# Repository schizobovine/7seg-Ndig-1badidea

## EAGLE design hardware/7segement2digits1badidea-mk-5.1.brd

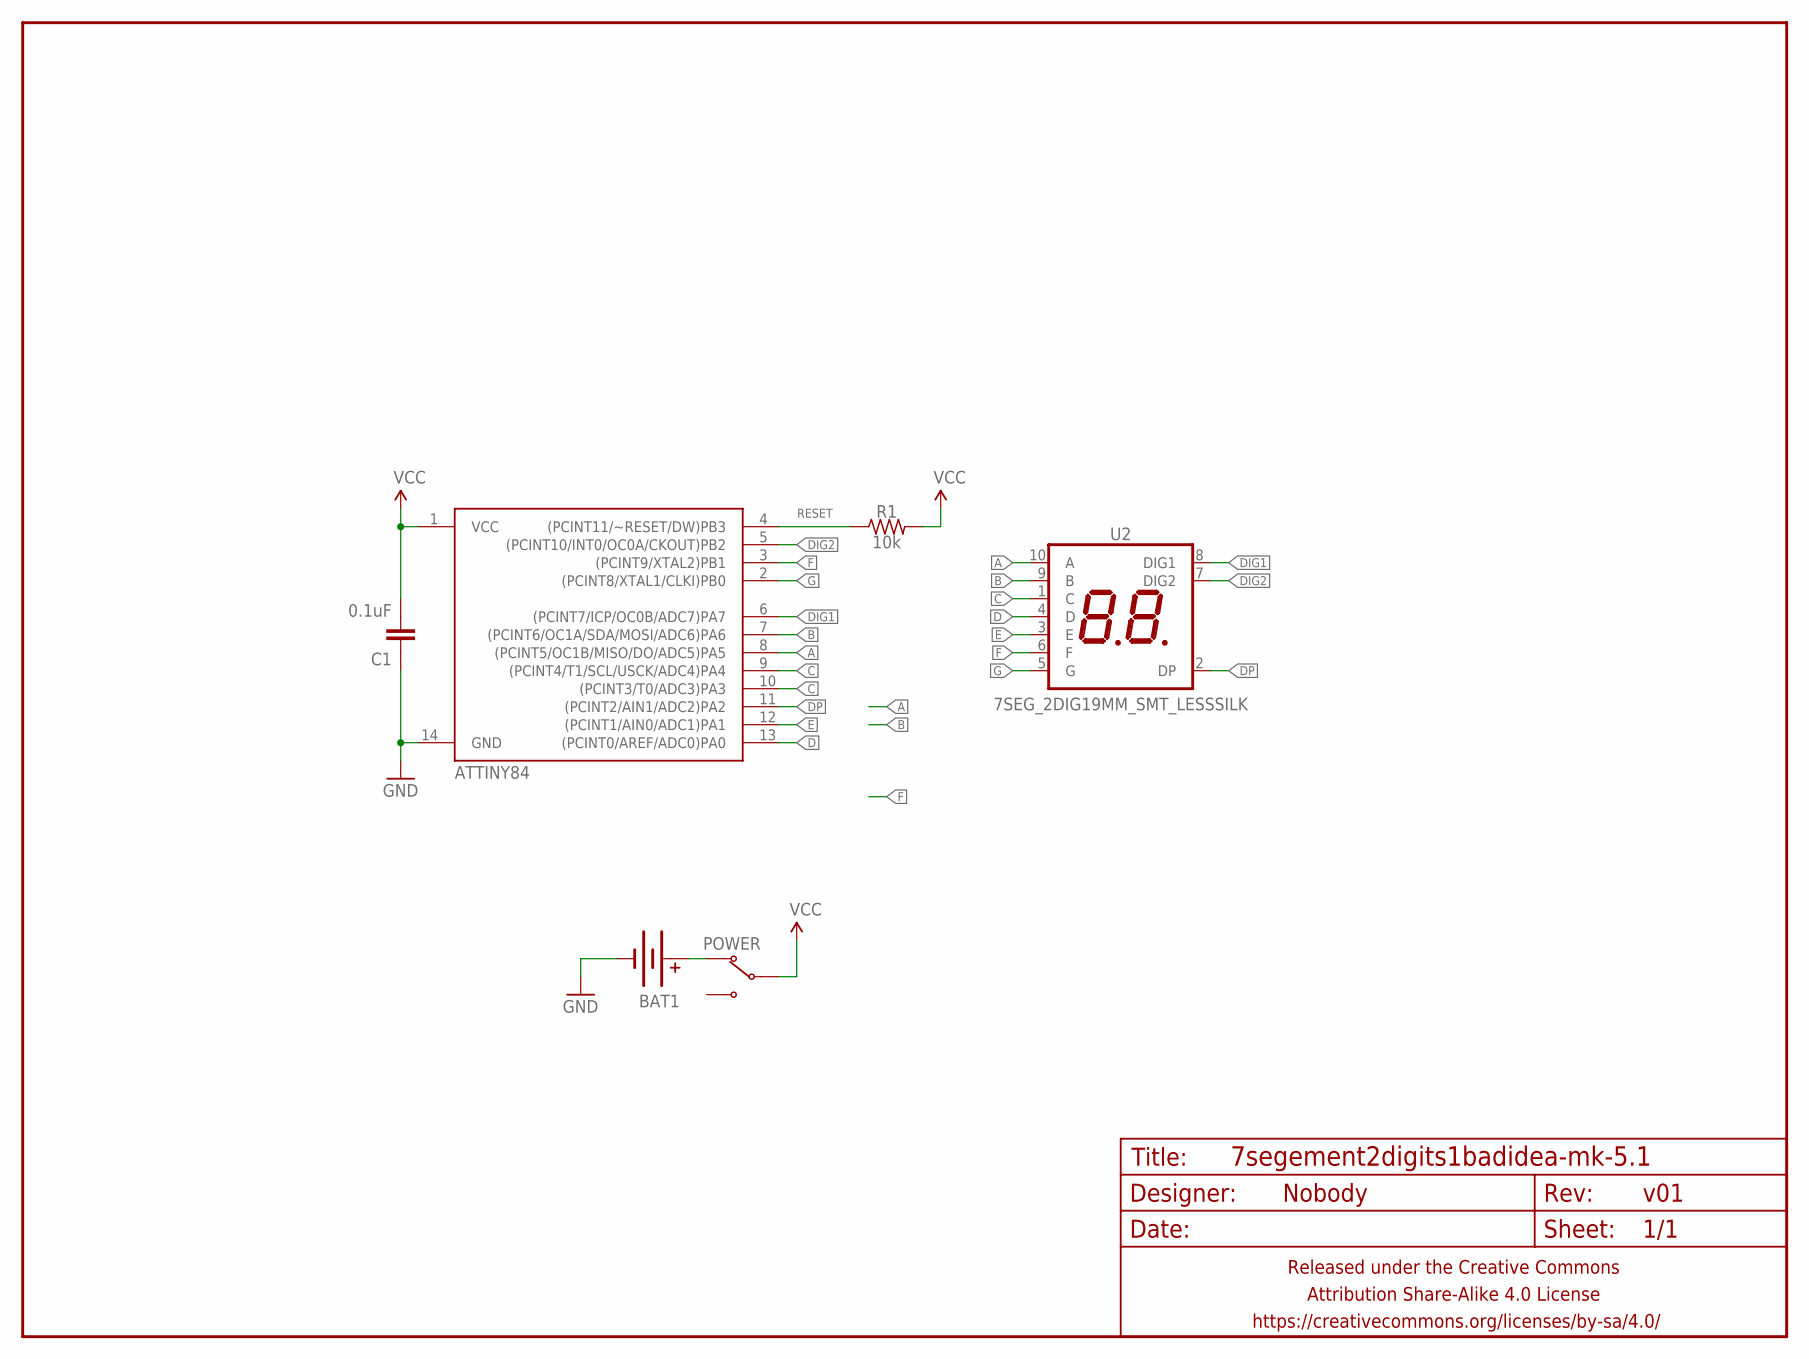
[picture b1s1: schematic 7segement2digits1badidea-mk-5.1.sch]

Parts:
BAT1: BATTERY20MM_SMD_TIGHT; BATTCON_20MM_MINE_STAHPIT
C1: 0.1uF; C0805
FRAME1: FRAME-LETTERNO_PACKAGE; DUMMY
POWER: SWITCH-SPDTPTH-RA-2.54MM; SPDT-RA-2.54MM
R1: 10k; R0805
U1: ATTINY84; SO14
U2: 7SEG_2DIG19MM_SMT_LESSSILK; 7SEG_2DIG_19MM_SMT_LESSSILK

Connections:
A: U1.8 ((PCINT5/OC1B/MISO/DO/ADC5)PA5), U2.10 (A)
B: U1.7 ((PCINT6/OC1A/SDA/MOSI/ADC6)PA6), U2.9 (B)
C: U1.9 ((PCINT4/T1/SCL/USCK/ADC4)PA4), U1.10 ((PCINT3/T0/ADC3)PA3), U2.1 (C)
D: U1.13 ((PCINT0/AREF/ADC0)PA0), U2.4 (D)
DIG1: U1.6 ((PCINT7/ICP/OC0B/ADC7)PA7), U2.8 (DIG1)
DIG2: U1.5 ((PCINT10/INT0/OC0A/CKOUT)PB2), U2.7 (DIG2)
DP: U1.11 ((PCINT2/AIN1/ADC2)PA2), U2.2 (DP)
E: U1.12 ((PCINT1/AIN0/ADC1)PA1), U2.3 (E)
F: U1.3 ((PCINT9/XTAL2)PB1), U2.6 (F)
G: U1.2 ((PCINT8/XTAL1/CLKI)PB0), U2.5 (G)
GND: BAT1.BOTTOM (-), C1.1, U1.14 (GND)
unnamed: BAT1.TOP@1 (+), BAT1.TOP@2 (+), POWER.1 (NC)
RESET: R1.1, U1.4 ((PCINT11/~RESET/DW)PB3)
VCC: C1.2, POWER.2 (COM), R1.2, U1.1 (VCC)

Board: 2 copper layers, 7 parts (1 on the bottom side), 14 nets, no tracks yet.

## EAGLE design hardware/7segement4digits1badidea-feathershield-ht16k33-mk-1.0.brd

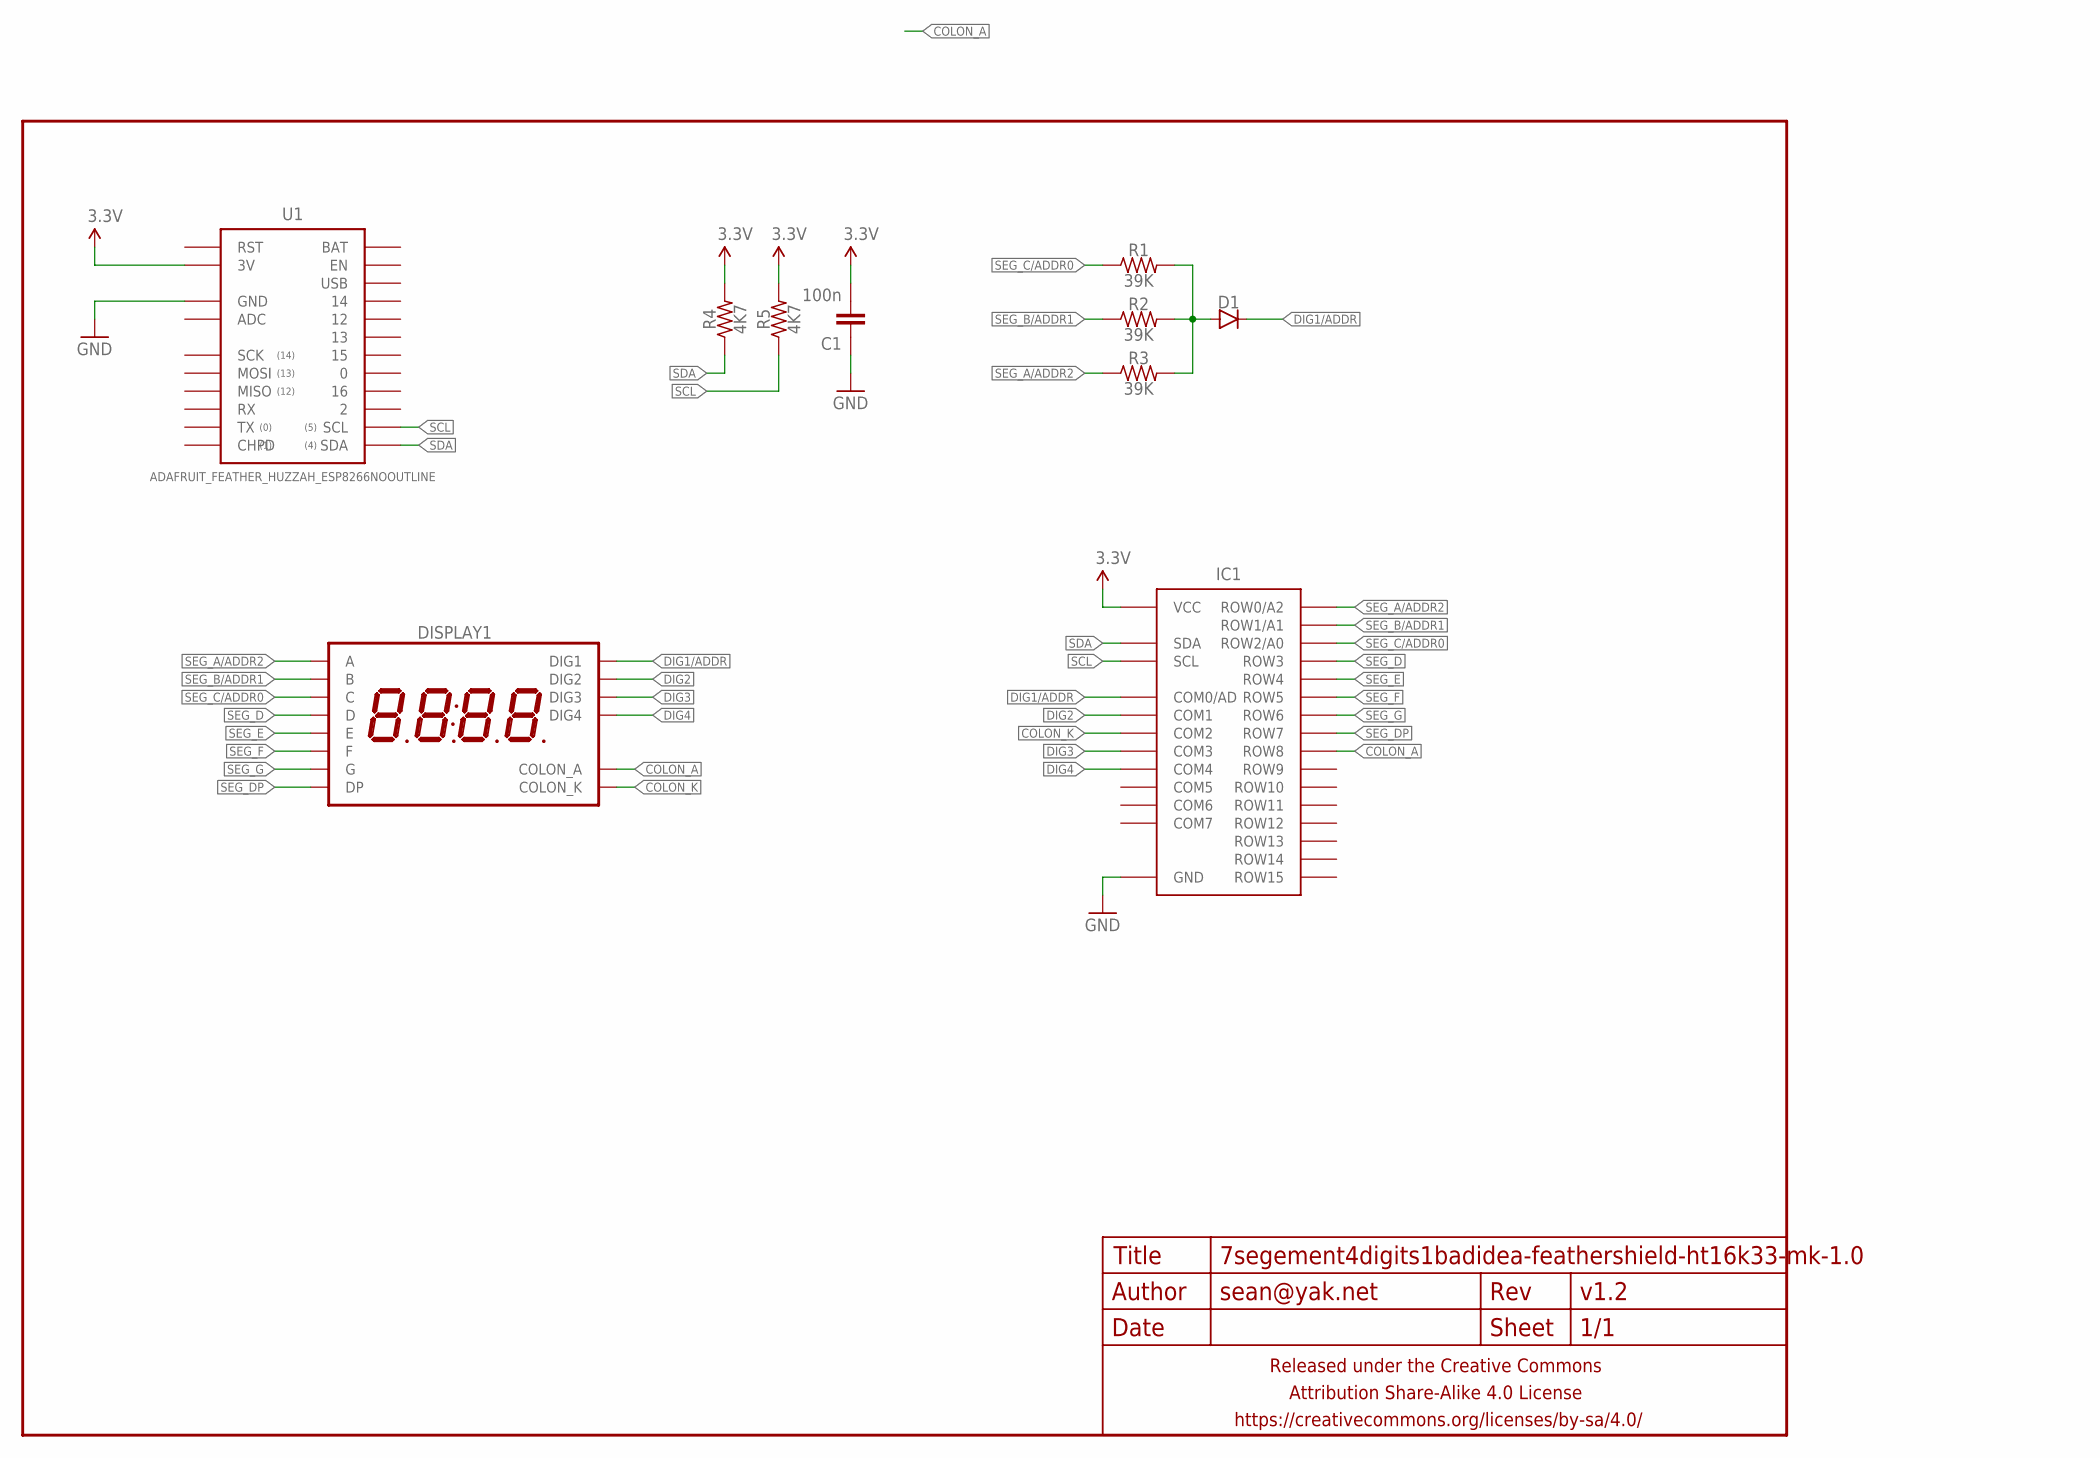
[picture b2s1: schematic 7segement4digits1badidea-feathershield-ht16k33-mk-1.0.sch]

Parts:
C1: 100n; C0603
D1: DIODESOD123; SOD123
DISPLAY1: 7SEG_4DIGIT_COLON14.2MM-CC; 7SEG_4DIG_0.56IN_14MM_ADAFRUIT
FRAME1: FRAME-LETTERNO_PACKAGE; DUMMY
IC1: HT16K33; SOIC28W
R1, R2, R3: 39K; R0603
R4, R5: 4K7; R0603
U1: ADAFRUIT_FEATHER_HUZZAH_ESP8266NOOUTLINE; ADAFRUIT_FEATHER_HUZZAH_NOOUTLINE

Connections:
3.3V: C1.2, IC1.28 (VCC), R4.2, R5.2, U1.3V
COLON_A: DISPLAY1.P$8 (COLON_A), IC1.17 (ROW8)
COLON_K: DISPLAY1.P$7 (COLON_K), IC1.4 (COM2)
DIG1/ADDR: D1.C, DISPLAY1.P$14 (DIG1), IC1.2 (COM0/AD)
DIG2: DISPLAY1.P$11 (DIG2), IC1.3 (COM1)
DIG3: DISPLAY1.P$10 (DIG3), IC1.5 (COM3)
DIG4: DISPLAY1.P$6 (DIG4), IC1.6 (COM4)
GND: C1.1, IC1.1 (GND), U1.GND@0 (GND)
unnamed: D1.A, R1.2, R2.2, R3.2
SCL: IC1.26 (SCL), R5.1, U1.SCL
SDA: IC1.27 (SDA), R4.1, U1.SDA
SEG_A/ADDR2: DISPLAY1.P$13 (A), IC1.25 (ROW0/A2), R3.1
SEG_B/ADDR1: DISPLAY1.P$9 (B), IC1.24 (ROW1/A1), R2.1
SEG_C/ADDR0: DISPLAY1.P$4 (C), IC1.23 (ROW2/A0), R1.1
SEG_D: DISPLAY1.P$2 (D), IC1.22 (ROW3)
SEG_DP: DISPLAY1.P$3 (DP), IC1.18 (ROW7)
SEG_E: DISPLAY1.P$1 (E), IC1.21 (ROW4)
SEG_F: DISPLAY1.P$12 (F), IC1.20 (ROW5)
SEG_G: DISPLAY1.P$5 (G), IC1.19 (ROW6)

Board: 2 copper layers, 11 parts (2 on the bottom side), 19 nets, no tracks yet.

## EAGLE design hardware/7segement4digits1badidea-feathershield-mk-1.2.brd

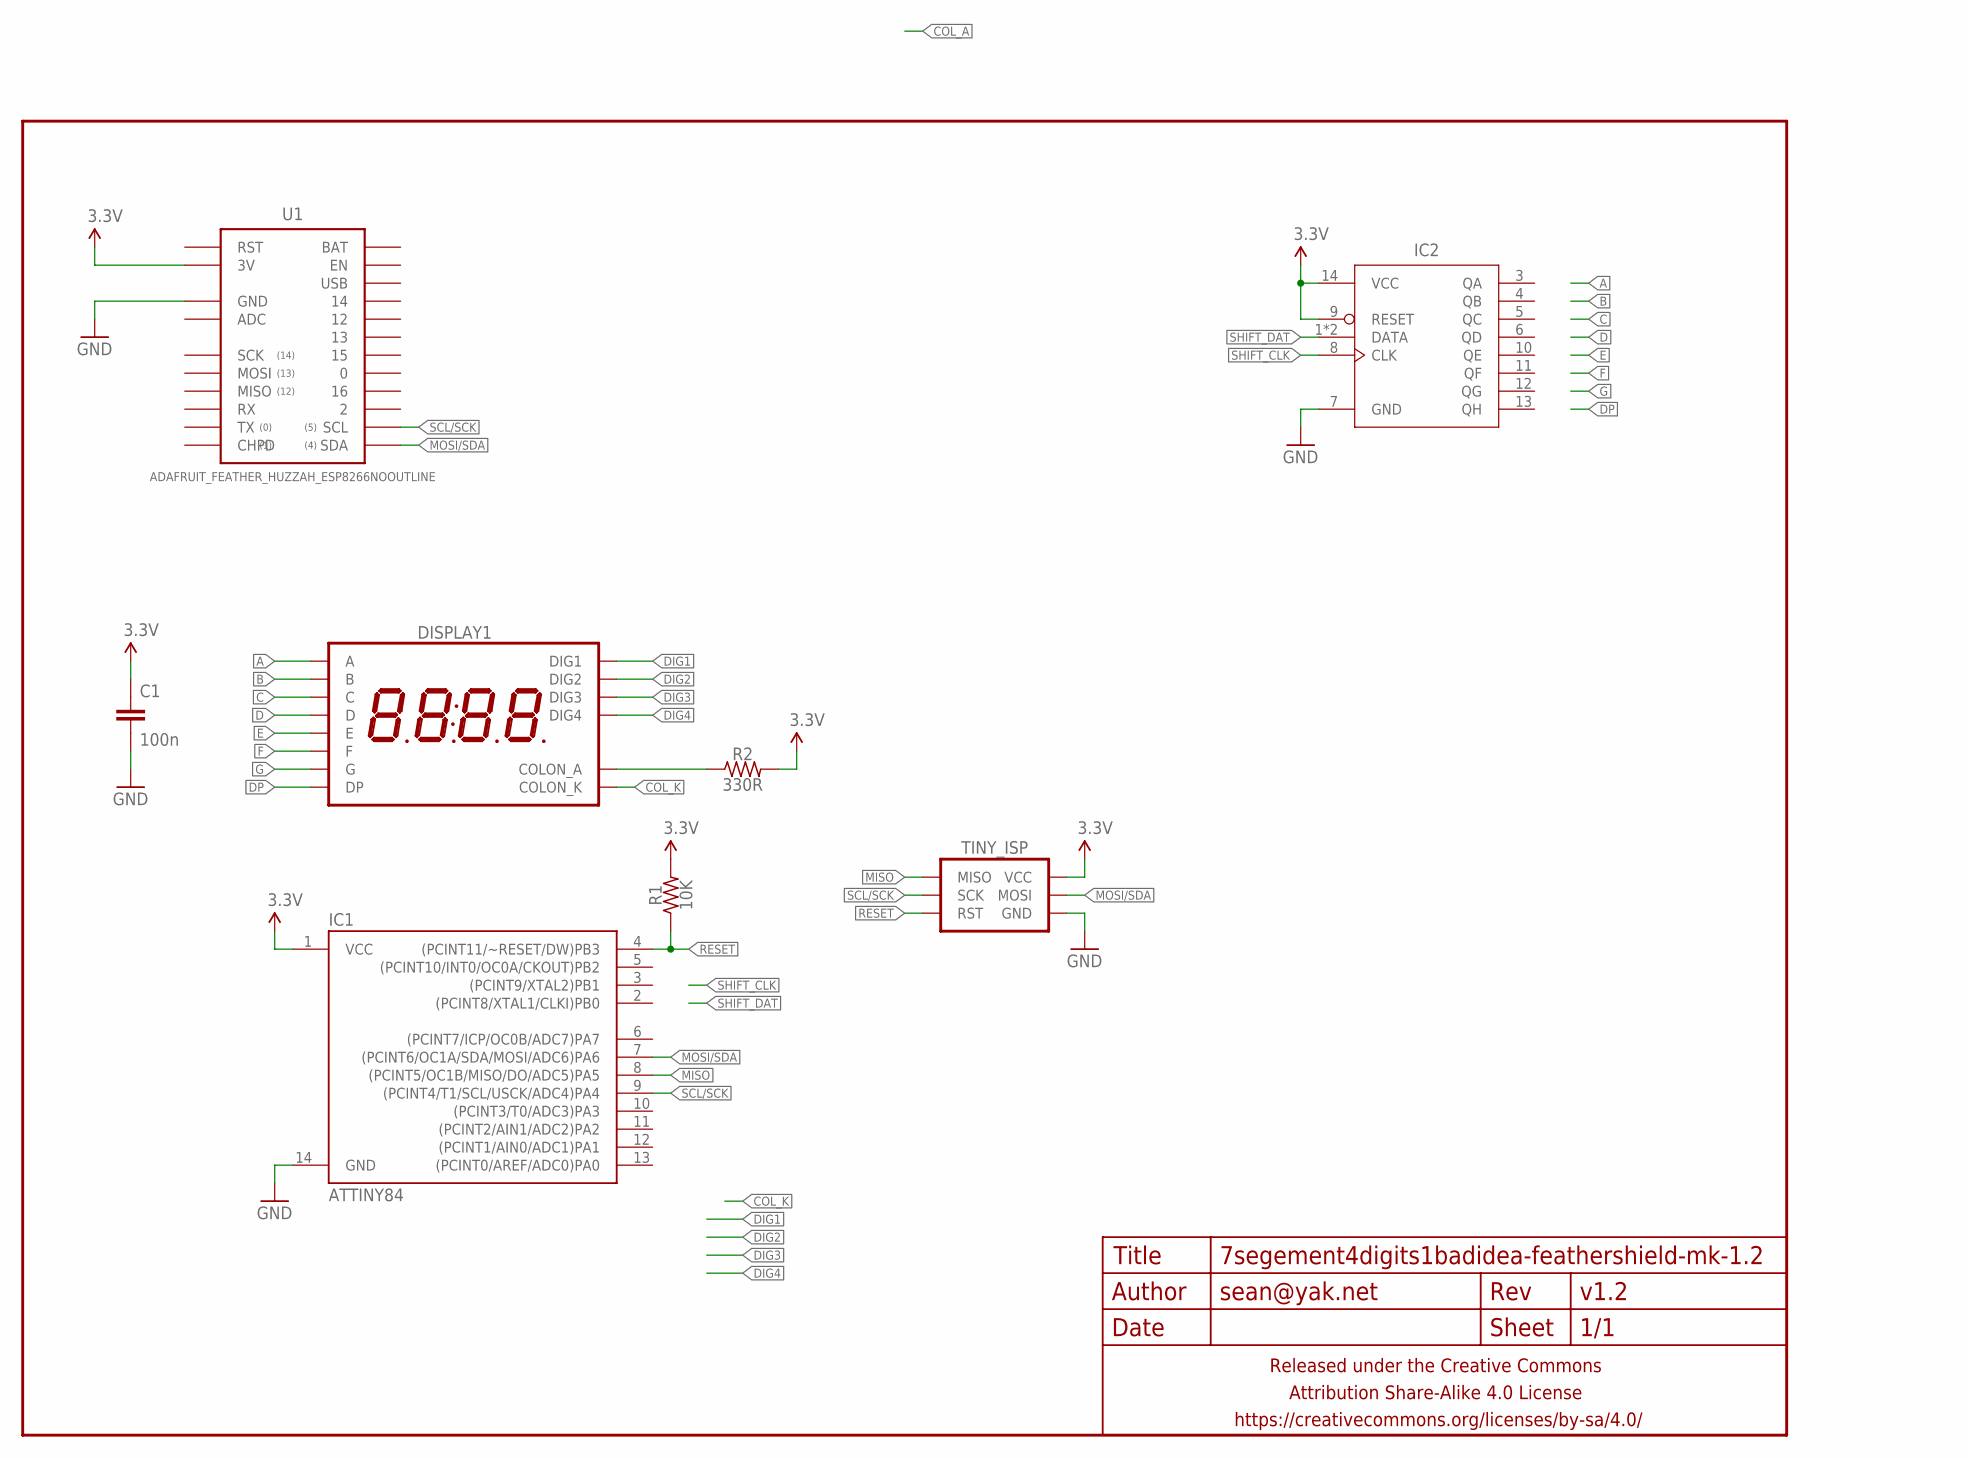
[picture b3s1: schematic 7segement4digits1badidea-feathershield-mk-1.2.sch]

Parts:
C1: 100n; C0603
DISPLAY1: 7SEG_4DIGIT_COLON14.2MM-CC; 7SEG_4DIG_0.56IN_14MM_ADAFRUIT
FRAME1: FRAME-LETTERNO_PACKAGE; DUMMY
IC1: ATTINY84; SO14
IC2: 74HC164; SO14
R1: 10K; R0603
R2: 330R; R0603
TINY_ISP: AVR_SPI_PRG_6TESTPOINTS; 2X3_TEST_POINTS
U1: ADAFRUIT_FEATHER_HUZZAH_ESP8266NOOUTLINE; ADAFRUIT_FEATHER_HUZZAH_NOOUTLINE

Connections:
3.3V: C1.1, IC1.1 (VCC), IC2.9 (RESET), IC2.14 (VCC), R1.2, R2.2, TINY_ISP.2 (VCC), U1.3V
A: DISPLAY1.P$13 (A)
B: DISPLAY1.P$9 (B)
C: DISPLAY1.P$4 (C)
COL_K: DISPLAY1.P$7 (COLON_K)
D: DISPLAY1.P$2 (D)
DIG1: DISPLAY1.P$14 (DIG1)
DIG2: DISPLAY1.P$11 (DIG2)
DIG3: DISPLAY1.P$10 (DIG3)
DIG4: DISPLAY1.P$6 (DIG4)
DP: DISPLAY1.P$3 (DP)
E: DISPLAY1.P$1 (E)
F: DISPLAY1.P$12 (F)
G: DISPLAY1.P$5 (G)
GND: C1.2, IC1.14 (GND), IC2.7 (GND), TINY_ISP.6 (GND), U1.GND@0 (GND)
MISO: IC1.8 ((PCINT5/OC1B/MISO/DO/ADC5)PA5), TINY_ISP.1 (MISO)
MOSI/SDA: IC1.7 ((PCINT6/OC1A/SDA/MOSI/ADC6)PA6), TINY_ISP.4 (MOSI), U1.SDA
unnamed: DISPLAY1.P$8 (COLON_A), R2.1
RESET: IC1.4 ((PCINT11/~RESET/DW)PB3), R1.1, TINY_ISP.5 (RST)
SCL/SCK: IC1.9 ((PCINT4/T1/SCL/USCK/ADC4)PA4), TINY_ISP.3 (SCK), U1.SCL
SHIFT_CLK: IC2.8 (CLK)
SHIFT_DAT: IC2.1 (DATA), IC2.2 (DATA)

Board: 2 copper layers, 9 parts (2 on the bottom side), 8 nets, no tracks yet.

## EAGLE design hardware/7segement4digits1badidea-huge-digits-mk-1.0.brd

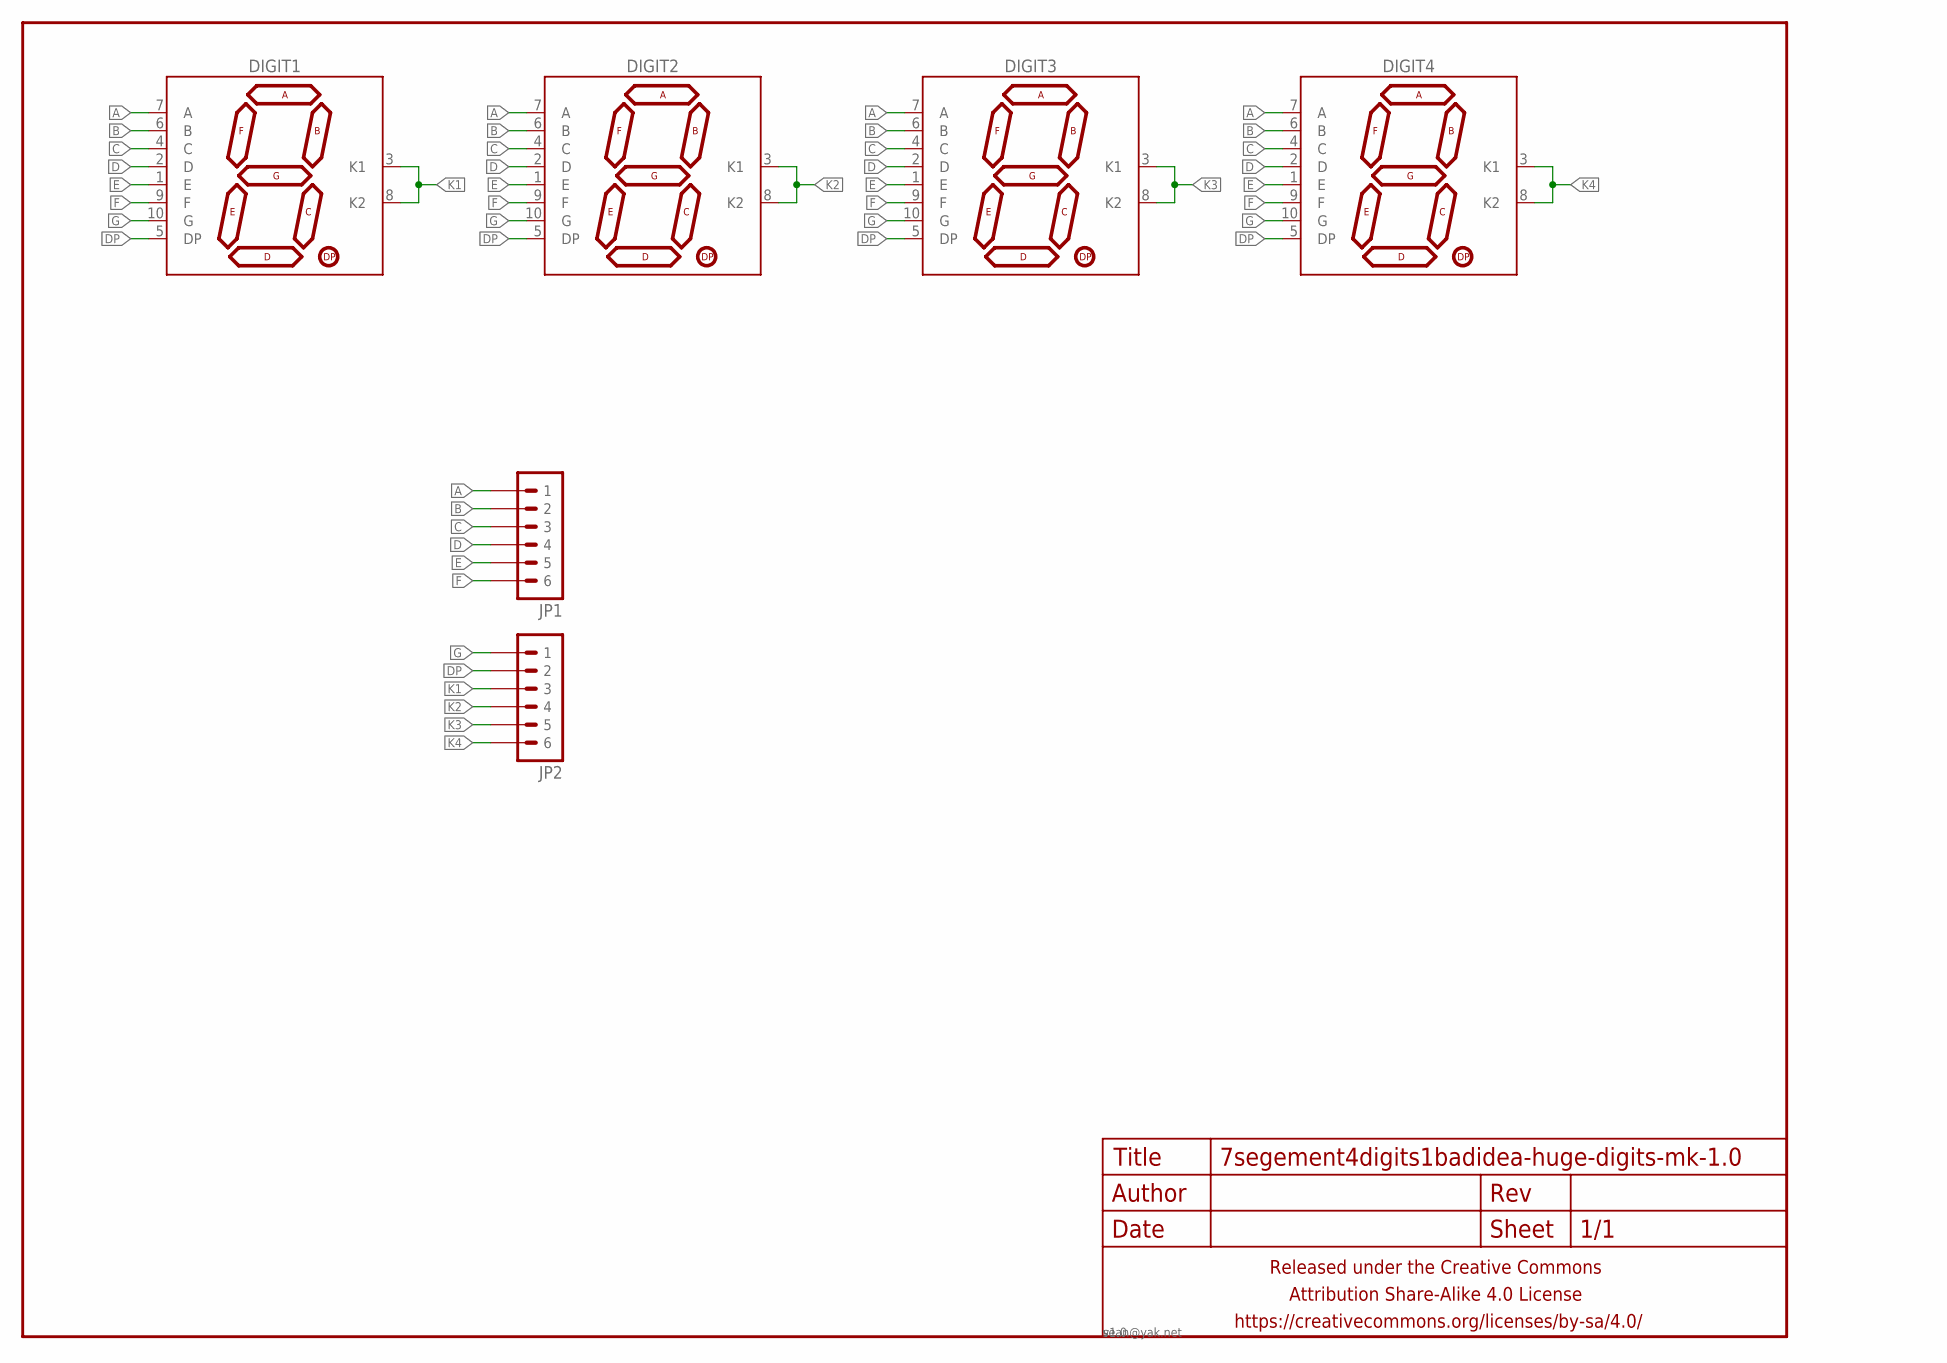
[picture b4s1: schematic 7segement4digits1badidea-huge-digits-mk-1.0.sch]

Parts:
DIGIT1, DIGIT2, DIGIT3, DIGIT4: 7SEG_1DIGPTH-25.4MM; 7SEG_1DIG_25.4MM
FRAME1: FRAME-LETTERNO_PACKAGE; DUMMY
JP1, JP2: M06PTH_CENTERED; 1X06_CENTERED

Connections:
A: DIGIT1.7 (A), DIGIT2.7 (A), DIGIT3.7 (A), DIGIT4.7 (A), JP1.1
B: DIGIT1.6 (B), DIGIT2.6 (B), DIGIT3.6 (B), DIGIT4.6 (B), JP1.2
C: DIGIT1.4 (C), DIGIT2.4 (C), DIGIT3.4 (C), DIGIT4.4 (C), JP1.3
D: DIGIT1.2 (D), DIGIT2.2 (D), DIGIT3.2 (D), DIGIT4.2 (D), JP1.4
DP: DIGIT1.5 (DP), DIGIT2.5 (DP), DIGIT3.5 (DP), DIGIT4.5 (DP), JP2.2
E: DIGIT1.1 (E), DIGIT2.1 (E), DIGIT3.1 (E), DIGIT4.1 (E), JP1.5
F: DIGIT1.9 (F), DIGIT2.9 (F), DIGIT3.9 (F), DIGIT4.9 (F), JP1.6
G: DIGIT1.10 (G), DIGIT2.10 (G), DIGIT3.10 (G), DIGIT4.10 (G), JP2.1
K1: DIGIT1.3 (K1), DIGIT1.8 (K2), JP2.3
K2: DIGIT2.3 (K1), DIGIT2.8 (K2), JP2.4
K3: DIGIT3.3 (K1), DIGIT3.8 (K2), JP2.5
K4: DIGIT4.3 (K1), DIGIT4.8 (K2), JP2.6

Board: 2 copper layers, 7 parts (0 on the bottom side), 12 nets, no tracks yet.

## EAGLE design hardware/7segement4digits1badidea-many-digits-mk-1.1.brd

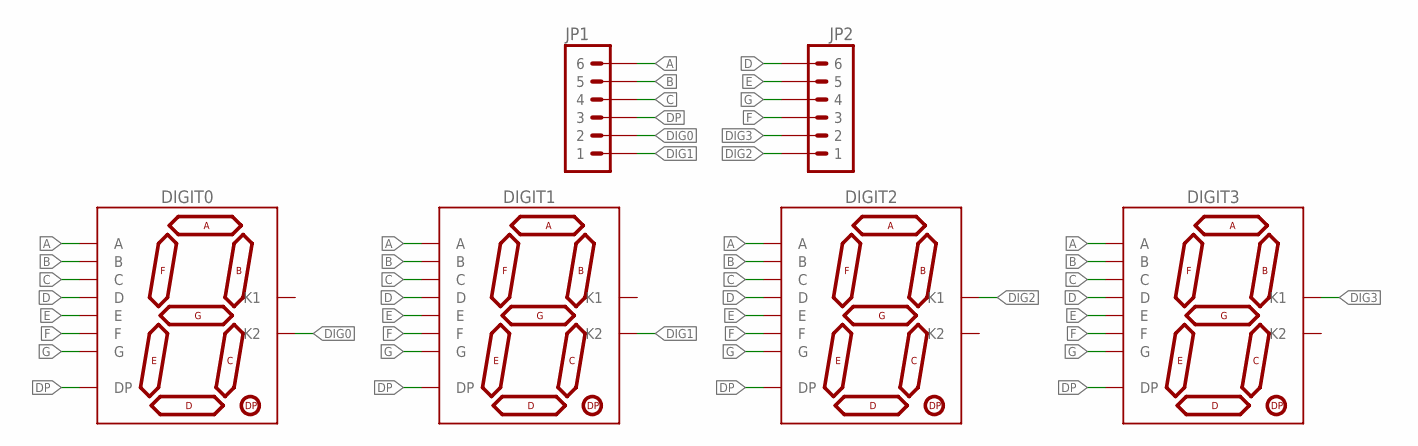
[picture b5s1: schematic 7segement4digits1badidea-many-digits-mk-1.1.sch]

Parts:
DIGIT0, DIGIT1, DIGIT2, DIGIT3: 7SEG_1DIGPTH-10MM; 7SEG_1DIG_10MM
JP1, JP2: M06-NOBS-PTH; 1X06_NOLOCK_FUCKITALL

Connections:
A: DIGIT0.10 (A), DIGIT1.10 (A), DIGIT2.10 (A), DIGIT3.10 (A), JP1.6
B: DIGIT0.9 (B), DIGIT1.9 (B), DIGIT2.9 (B), DIGIT3.9 (B), JP1.5
C: DIGIT0.8 (C), DIGIT1.8 (C), DIGIT2.8 (C), DIGIT3.8 (C), JP1.4
D: DIGIT0.5 (D), DIGIT1.5 (D), DIGIT2.5 (D), DIGIT3.5 (D), JP2.6
DIG0: DIGIT0.6 (K2), JP1.2
DIG1: DIGIT1.6 (K2), JP1.1
DIG2: DIGIT2.1 (K1), JP2.1
DIG3: DIGIT3.1 (K1), JP2.2
DP: DIGIT0.7 (DP), DIGIT1.7 (DP), DIGIT2.7 (DP), DIGIT3.7 (DP), JP1.3
E: DIGIT0.4 (E), DIGIT1.4 (E), DIGIT2.4 (E), DIGIT3.4 (E), JP2.5
F: DIGIT0.2 (F), DIGIT1.2 (F), DIGIT2.2 (F), DIGIT3.2 (F), JP2.3
G: DIGIT0.3 (G), DIGIT1.3 (G), DIGIT2.3 (G), DIGIT3.3 (G), JP2.4

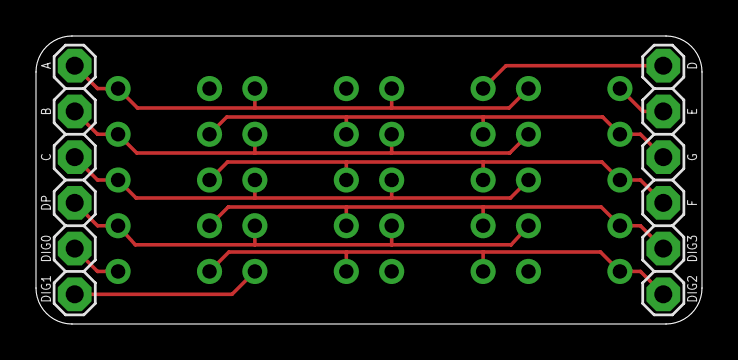
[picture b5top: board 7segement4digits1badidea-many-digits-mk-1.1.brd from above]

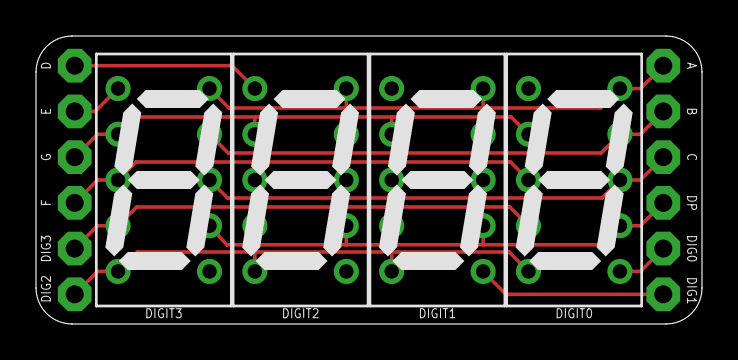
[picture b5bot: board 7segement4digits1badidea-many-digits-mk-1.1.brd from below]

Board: 2 copper layers, 37.0 x 16.0 mm, 6 parts (4 on the bottom side), 12 nets.

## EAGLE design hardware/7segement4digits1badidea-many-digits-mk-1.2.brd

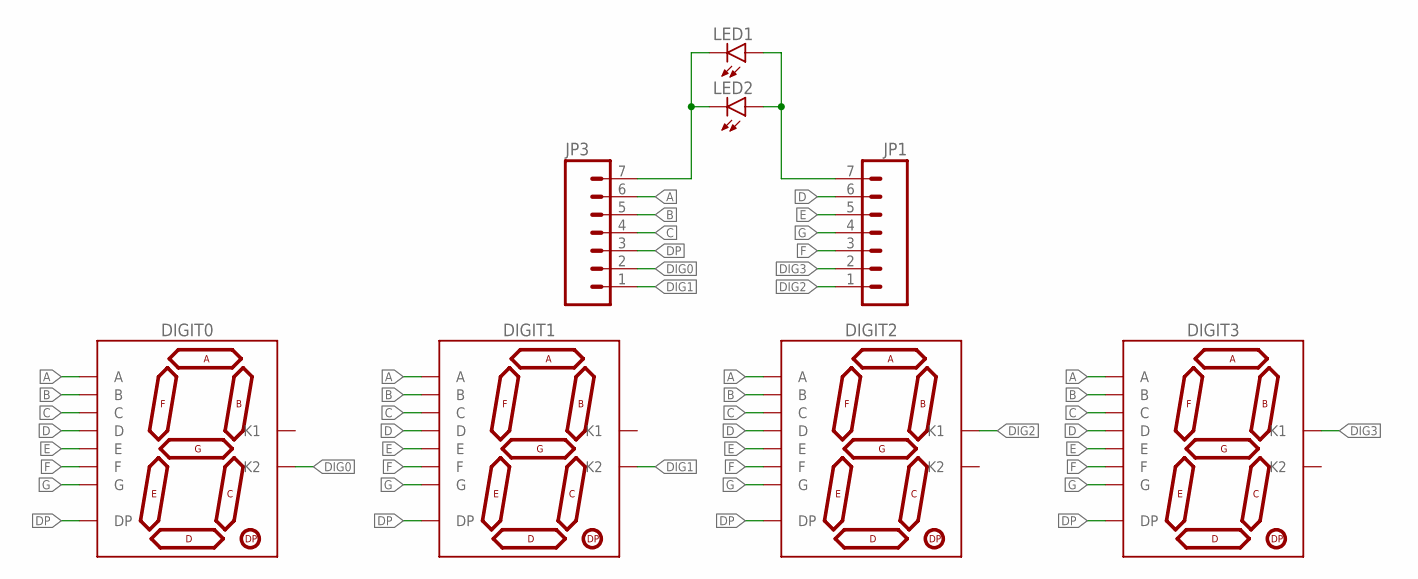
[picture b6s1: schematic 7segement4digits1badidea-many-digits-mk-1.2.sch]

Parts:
DIGIT0, DIGIT1, DIGIT2, DIGIT3: 7SEG_1DIGPTH-10MM; 7SEG_1DIG_10MM
JP1, JP3: M07; 1X07
LED1, LED2: LED3MM-LESS; LED3MM-LESSSILK

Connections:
A: DIGIT0.10 (A), DIGIT1.10 (A), DIGIT2.10 (A), DIGIT3.10 (A), JP3.6
B: DIGIT0.9 (B), DIGIT1.9 (B), DIGIT2.9 (B), DIGIT3.9 (B), JP3.5
C: DIGIT0.8 (C), DIGIT1.8 (C), DIGIT2.8 (C), DIGIT3.8 (C), JP3.4
D: DIGIT0.5 (D), DIGIT1.5 (D), DIGIT2.5 (D), DIGIT3.5 (D), JP1.6
DIG0: DIGIT0.6 (K2), JP3.2
DIG1: DIGIT1.6 (K2), JP3.1
DIG2: DIGIT2.1 (K1), JP1.1
DIG3: DIGIT3.1 (K1), JP1.2
DP: DIGIT0.7 (DP), DIGIT1.7 (DP), DIGIT2.7 (DP), DIGIT3.7 (DP), JP3.3
E: DIGIT0.4 (E), DIGIT1.4 (E), DIGIT2.4 (E), DIGIT3.4 (E), JP1.5
F: DIGIT0.2 (F), DIGIT1.2 (F), DIGIT2.2 (F), DIGIT3.2 (F), JP1.3
G: DIGIT0.3 (G), DIGIT1.3 (G), DIGIT2.3 (G), DIGIT3.3 (G), JP1.4
unnamed: JP3.7, LED1.K (C), LED2.K (C)
unnamed: JP1.7, LED1.A, LED2.A

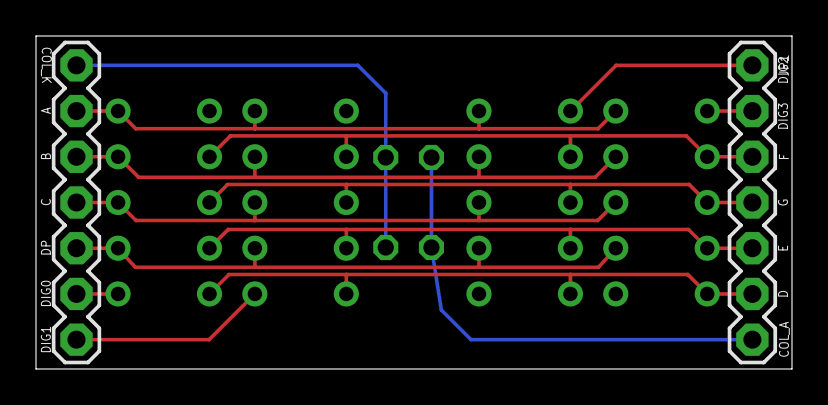
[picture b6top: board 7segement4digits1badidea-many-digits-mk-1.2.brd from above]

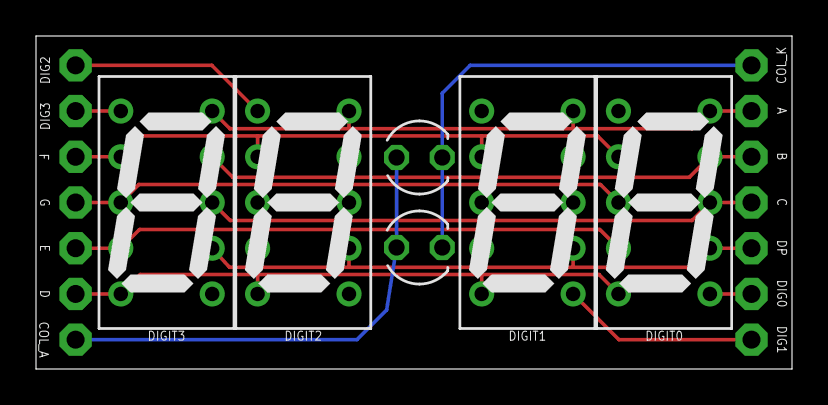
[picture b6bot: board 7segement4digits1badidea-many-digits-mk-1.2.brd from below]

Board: 2 copper layers, 42.0 x 18.5 mm, 8 parts (6 on the bottom side), 14 nets.

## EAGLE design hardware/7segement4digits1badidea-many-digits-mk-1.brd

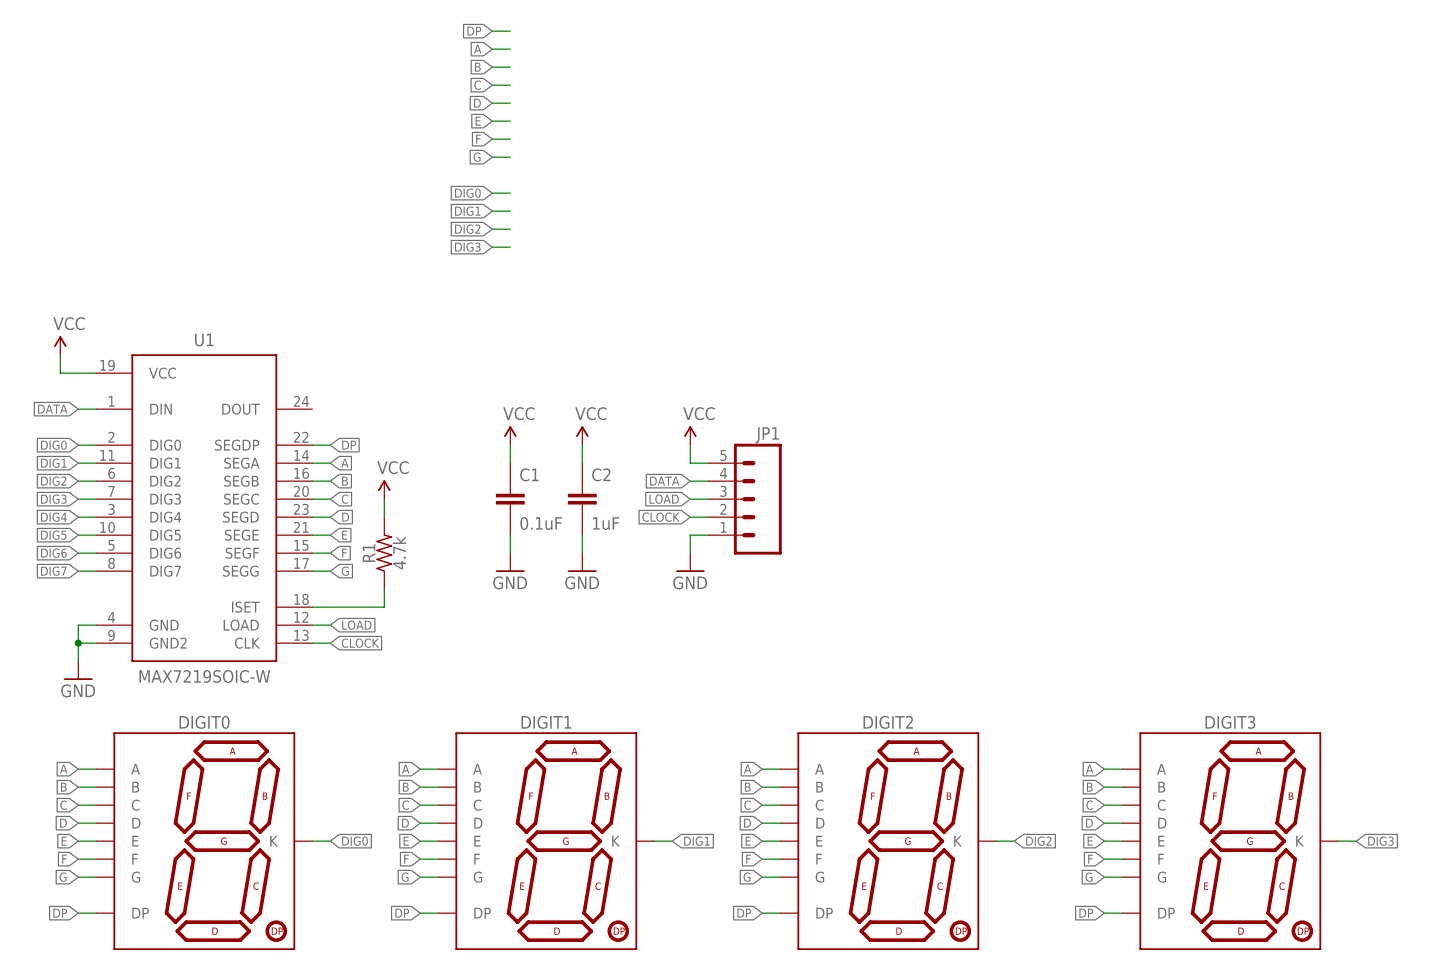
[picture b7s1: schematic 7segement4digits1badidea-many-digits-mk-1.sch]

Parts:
C1: 0.1uF; C0603
C2: 1uF; C0805
DIGIT0, DIGIT1, DIGIT2, DIGIT3: 7SEG_1DIGPTH-10MM; 7SEG_1DIG_10MM
JP1: M05JST-PH-VERT-PTH; JST-5-PH-VERT-PTH
R1: 4.7k; R0603
U1: MAX7219SOIC-W; SO24W

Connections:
A: DIGIT0.10 (A), DIGIT1.10 (A), DIGIT2.10 (A), DIGIT3.10 (A), U1.14 (SEGA)
B: DIGIT0.9 (B), DIGIT1.9 (B), DIGIT2.9 (B), DIGIT3.9 (B), U1.16 (SEGB)
C: DIGIT0.8 (C), DIGIT1.8 (C), DIGIT2.8 (C), DIGIT3.8 (C), U1.20 (SEGC)
CLOCK: JP1.2, U1.13 (CLK)
D: DIGIT0.5 (D), DIGIT1.5 (D), DIGIT2.5 (D), DIGIT3.5 (D), U1.23 (SEGD)
DATA: JP1.4, U1.1 (DIN)
DIG0: DIGIT0.1 (K), DIGIT0.6 (K), U1.2 (DIG0)
DIG1: DIGIT1.1 (K), DIGIT1.6 (K), U1.11 (DIG1)
DIG2: DIGIT2.1 (K), DIGIT2.6 (K), U1.6 (DIG2)
DIG3: DIGIT3.1 (K), DIGIT3.6 (K), U1.7 (DIG3)
DIG4: U1.3 (DIG4)
DIG5: U1.10 (DIG5)
DIG6: U1.5 (DIG6)
DIG7: U1.8 (DIG7)
DP: DIGIT0.7 (DP), DIGIT1.7 (DP), DIGIT2.7 (DP), DIGIT3.7 (DP), U1.22 (SEGDP)
E: DIGIT0.4 (E), DIGIT1.4 (E), DIGIT2.4 (E), DIGIT3.4 (E), U1.21 (SEGE)
F: DIGIT0.2 (F), DIGIT1.2 (F), DIGIT2.2 (F), DIGIT3.2 (F), U1.15 (SEGF)
G: DIGIT0.3 (G), DIGIT1.3 (G), DIGIT2.3 (G), DIGIT3.3 (G), U1.17 (SEGG)
GND: C1.2, C2.2, JP1.1, U1.4 (GND), U1.9 (GND2)
LOAD: JP1.3, U1.12 (LOAD)
unnamed: R1.1, U1.18 (ISET)
VCC: C1.1, C2.1, JP1.5, R1.2, U1.19 (VCC)

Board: 2 copper layers, 9 parts (4 on the bottom side), 18 nets, no tracks yet.

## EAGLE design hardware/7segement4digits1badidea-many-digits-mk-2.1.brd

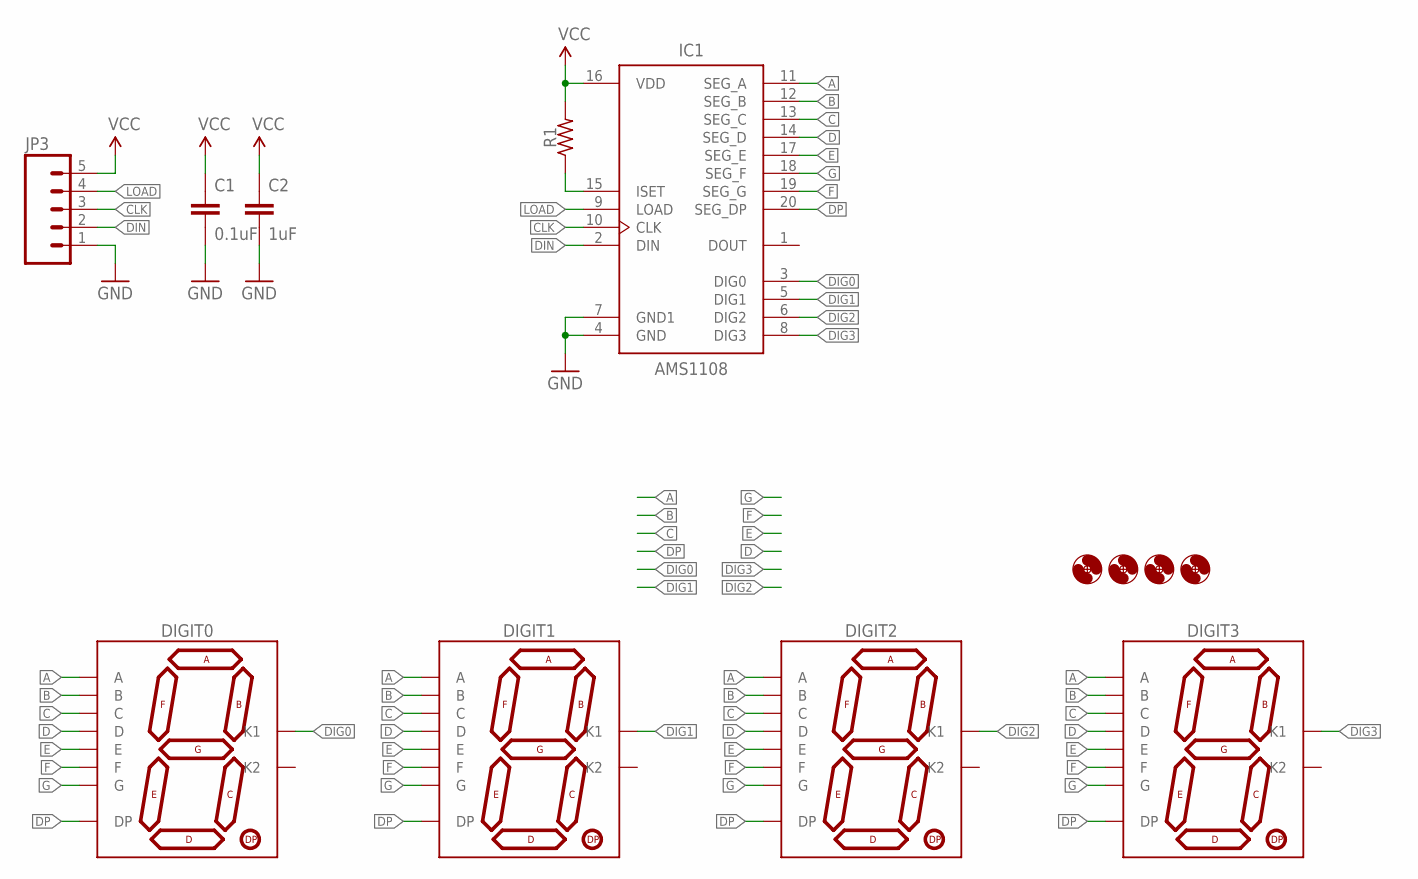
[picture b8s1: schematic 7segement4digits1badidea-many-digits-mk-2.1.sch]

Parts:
C1: 0.1uF; C0603
C2: 1uF; C0805
DIGIT0, DIGIT1, DIGIT2, DIGIT3: 7SEG_1DIGPTH-25.4MM; 7SEG_1DIG_25.4MM
H1, H2, H3, H4: HOLE#2; HOLE-#2
IC1: AMS1108; SO20W-NOSUCK
JP3: M05PTH; 1X05
R1: RESISTORR0603; R0603

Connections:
A: DIGIT0.7 (A), DIGIT1.7 (A), DIGIT2.7 (A), DIGIT3.7 (A), IC1.11 (SEG_A)
B: DIGIT0.6 (B), DIGIT1.6 (B), DIGIT2.6 (B), DIGIT3.6 (B), IC1.12 (SEG_B)
C: DIGIT0.4 (C), DIGIT1.4 (C), DIGIT2.4 (C), DIGIT3.4 (C), IC1.13 (SEG_C)
CLK: IC1.10 (CLK), JP3.3
D: DIGIT0.2 (D), DIGIT1.2 (D), DIGIT2.2 (D), DIGIT3.2 (D), IC1.14 (SEG_D)
DIG0: DIGIT0.3 (K1), IC1.3 (DIG0)
DIG1: DIGIT1.3 (K1), IC1.5 (DIG1)
DIG2: DIGIT2.3 (K1), IC1.6 (DIG2)
DIG3: DIGIT3.3 (K1), IC1.8 (DIG3)
DIN: IC1.2 (DIN), JP3.2
DP: DIGIT0.5 (DP), DIGIT1.5 (DP), DIGIT2.5 (DP), DIGIT3.5 (DP), IC1.20 (SEG_DP)
E: DIGIT0.1 (E), DIGIT1.1 (E), DIGIT2.1 (E), DIGIT3.1 (E), IC1.17 (SEG_E)
F: DIGIT0.9 (F), DIGIT1.9 (F), DIGIT2.9 (F), DIGIT3.9 (F), IC1.19 (SEG_G)
G: DIGIT0.10 (G), DIGIT1.10 (G), DIGIT2.10 (G), DIGIT3.10 (G), IC1.18 (SEG_F)
GND: C1.2, C2.2, IC1.4 (GND), IC1.7 (GND1), JP3.1
LOAD: IC1.9 (LOAD), JP3.4
unnamed: IC1.15 (ISET), R1.1
VCC: C1.1, C2.1, IC1.16 (VDD), JP3.5, R1.2

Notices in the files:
parts and their libraries:
SparkFun-Aesthetics: Licensing: Creative Commons ShareAlike 4.0 International - https://creativecommons.org/licenses/by-sa/4.0
A_butts: Released under the Creative Commons Attribution Share-Alike 4.0 License
A_butts: https://creativecommons.org/licenses/by-sa/4.0
